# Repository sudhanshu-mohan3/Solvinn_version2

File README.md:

# VerveFlo

Pneumatic Compression Therapy Device firmware
ESP32-S3 · Arduino IDE

## Hardware
- ESP32-S3 Dev Module
- SH1106 OLED 128x64 (I2C)
- HX710B Pressure Sensor
- 5x Fill Solenoid Valves + 1x Release Valve (normally-open)
- 5V DC Pump Motor
- 2S 18650 Li-Ion Battery

## Pin Map
| Component       | GPIO |
|----------------|------|
| Fill Valve 1   | 26   |
| Fill Valve 2   | 47   |
| Fill Valve 3   | 39   |
| Fill Valve 4   | 40   |
| Fill Valve 5   | 41   |
| Release Valve  | 42   |
| Pump Motor     | 21   |
| HX710B Dout    | 34   |
| HX710B SCK     | 33   |
| LED            | 3    |
| Battery ADC    | 15   |
| BTN Start      | 35   |
| BTN Mode       | 36   |
| BTN Pressure   | 37   |
| BTN Time       | 48   |

## Libraries Required
- U8g2 by olikraus
- Q2HX711 by bogde (Queuetue_HX711_Library)
- WiFi / WebServer / DNSServer / Preferences — built into ESP32 core

## Board Settings
- Board: ESP32S3 Dev Module
- USB CDC On Boot: Enabled
- Partition: Default 4MB with spiffs

## Files
| File | Purpose |
|------|---------|
| verveflo.ino | Main firmware — flash this |
| verveflo_hwtest.ino | Hardware test — no libraries needed |
| verveflo_pressure_cal.ino | Pressure sensor calibration |
| verveflo_valve_test.ino | Valve test with OLED |

## First Time Setup
1. Flash verveflo.ino
2. Connect phone to WiFi hotspot: VerveFlo-Setup
3. Open 192.168.4.1 → enter your WiFi password
4. Open browser → http://[device IP]
5. Serial: type zero at atmosphere
6. Serial: type selftest to verify hardware

## Serial Monitor
115200 baud · Newline line ending
Type help for full command list

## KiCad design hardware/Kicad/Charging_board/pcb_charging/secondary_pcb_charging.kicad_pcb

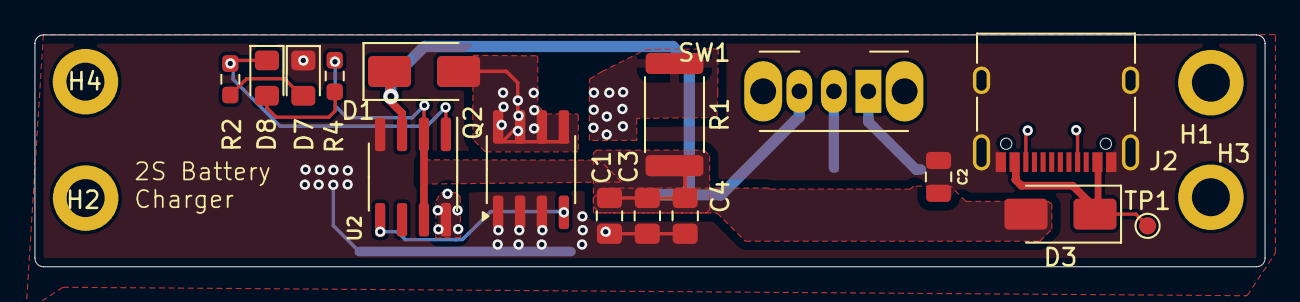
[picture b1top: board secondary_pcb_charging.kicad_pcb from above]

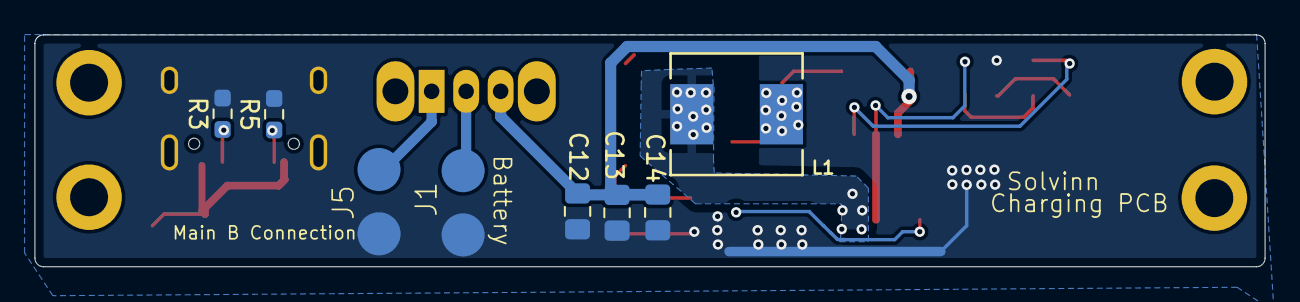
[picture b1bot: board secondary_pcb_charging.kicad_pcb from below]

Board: 2 copper layers, 71.3 x 13.4 mm, 28 parts (8 on the bottom side), 14 nets.

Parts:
C1, C3, C4, C12, C13, C14: 100nf; C_0805_2012Metric_Pad1.18x1.45mm_HandSolder
C2: 1uF_0805; C_0805_2012Metric
D1: SS34; D_SMA
D3: SS14; D_SMA
D7: RED LED; LED_0805_2012Metric_Pad1.15x1.40mm_HandSolder
D8: GREEN LED; LED_0805_2012Metric_Pad1.15x1.40mm_HandSolder
H1, H2, H3, H4: MountingHole; MountingHole_2.2mm_M2_DIN965_Pad
J1, J5: JST-S2B-XH_Sideentry; Solder_pad2
J2: USB_C_Receptacle_USB2.0_16P; USB_C_Receptacle_XKB_U262-16XN-4BVC11
L1: 10uh; LMLP07A7M1R0DTAS_AVX
Q2: IRF7832; SOIC-8_3.9x4.9mm_P1.27mm
R1: 50mohm_2512; R_2512
R2, R4: 2.2k; R_0603_1608Metric_Pad0.98x0.95mm_HandSolder
R3, R5: 5.1K; R_0603_1608Metric_Pad0.98x0.95mm_HandSolder
SW1: SW_Slide_SPDT_Straight_CK_OS102011MS2Q; SW_Slide_SPDT_Angled_CK_OS102011MA1Q
TP1: TestPoint; TestPoint_Pad_D1.0mm
U2: CN3302; SOIC-8_3.9x4.9mm_P1.27mm

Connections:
/8.4: J5.2, SW1.1 (C)
/ Battery_out: J1.2, SW1.2 (B)
/VBAT: C12.2, C13.2, C14.2, D1.1 (K), SW1.3 (A), U2.3 (BAT)
/cc1: J2.A5 (CC1), R3.1
/cc2: J2.B5 (CC2), R5.1
GND: C1.2, C2.1, C2.2, C3.2, C4.2, C12.1, C13.1, C14.1, D7.1 (K), J1.1, J2.A1 (GND), J2.A12 (GND), J2.B1 (GND), J2.B12 (GND), J2.S1 (SHIELD), J5.1, Q2.1 (S), Q2.2 (S), Q2.3 (S), R3.2, R5.2, U2.4 (GND)
unnamed: D1.2 (A), L1.2, Q2.5 (D), Q2.6 (D), Q2.7 (D), Q2.8 (D)
unnamed: D3.1 (K), J2.A4 (VBUS), J2.A9 (VBUS), J2.B4 (VBUS), J2.B9 (VBUS), TP1.1
unnamed: D7.2 (A), R2.1
unnamed: D8.2 (A), R4.1
unnamed: D8.1 (K), R2.2, U2.1 (STAT)
unnamed: Q2.4 (G), U2.5 (LDRV)
unnamed: L1.1, R1.1, U2.8 (CSN)
VBUS: C1.1, C3.1, C4.1, D3.2 (A), R1.2, R4.2, U2.2 (CE), U2.7 (VIN)

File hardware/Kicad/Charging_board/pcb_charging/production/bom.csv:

Designator,Footprint,Quantity,Value,LCSC Part #
"C1, C12, C13, C14, C3, C4",0805,6,100nf,
C2,0805,1,1uF_0805,
D1,D_SMA,1,SS34,
D3,D_SMA,1,SS14,
D7,0805,1,RED LED,
D8,0805,1,GREEN LED,
"J1, J5",Solder_pad2,2,JST-S2B-XH_Sideentry,
J2,USB_C_Receptacle_XKB_U262-16XN-4BVC11,1,USB_C_Receptacle_USB2.0_16P,
L1,LMLP07A7M1R0DTAS_AVX,1,10uh,
Q2,SOIC-8_3.9x4.9mm_P1.27mm,1,IRF7832,
R1,R_2512,1,50mohm_2512,
"R2, R4",0603,2,2.2k,
"R3, R5",0603,2,5.1K,
SW1,SW_Slide_SPDT_Angled_CK_OS102011MA1Q,1,SW_Slide_SPDT_Straight_CK_OS102011MS2Q,
TP1,TestPoint_Pad_D1.0mm,1,TestPoint,
U2,SOIC-8_3.9x4.9mm_P1.27mm,1,CN3302,

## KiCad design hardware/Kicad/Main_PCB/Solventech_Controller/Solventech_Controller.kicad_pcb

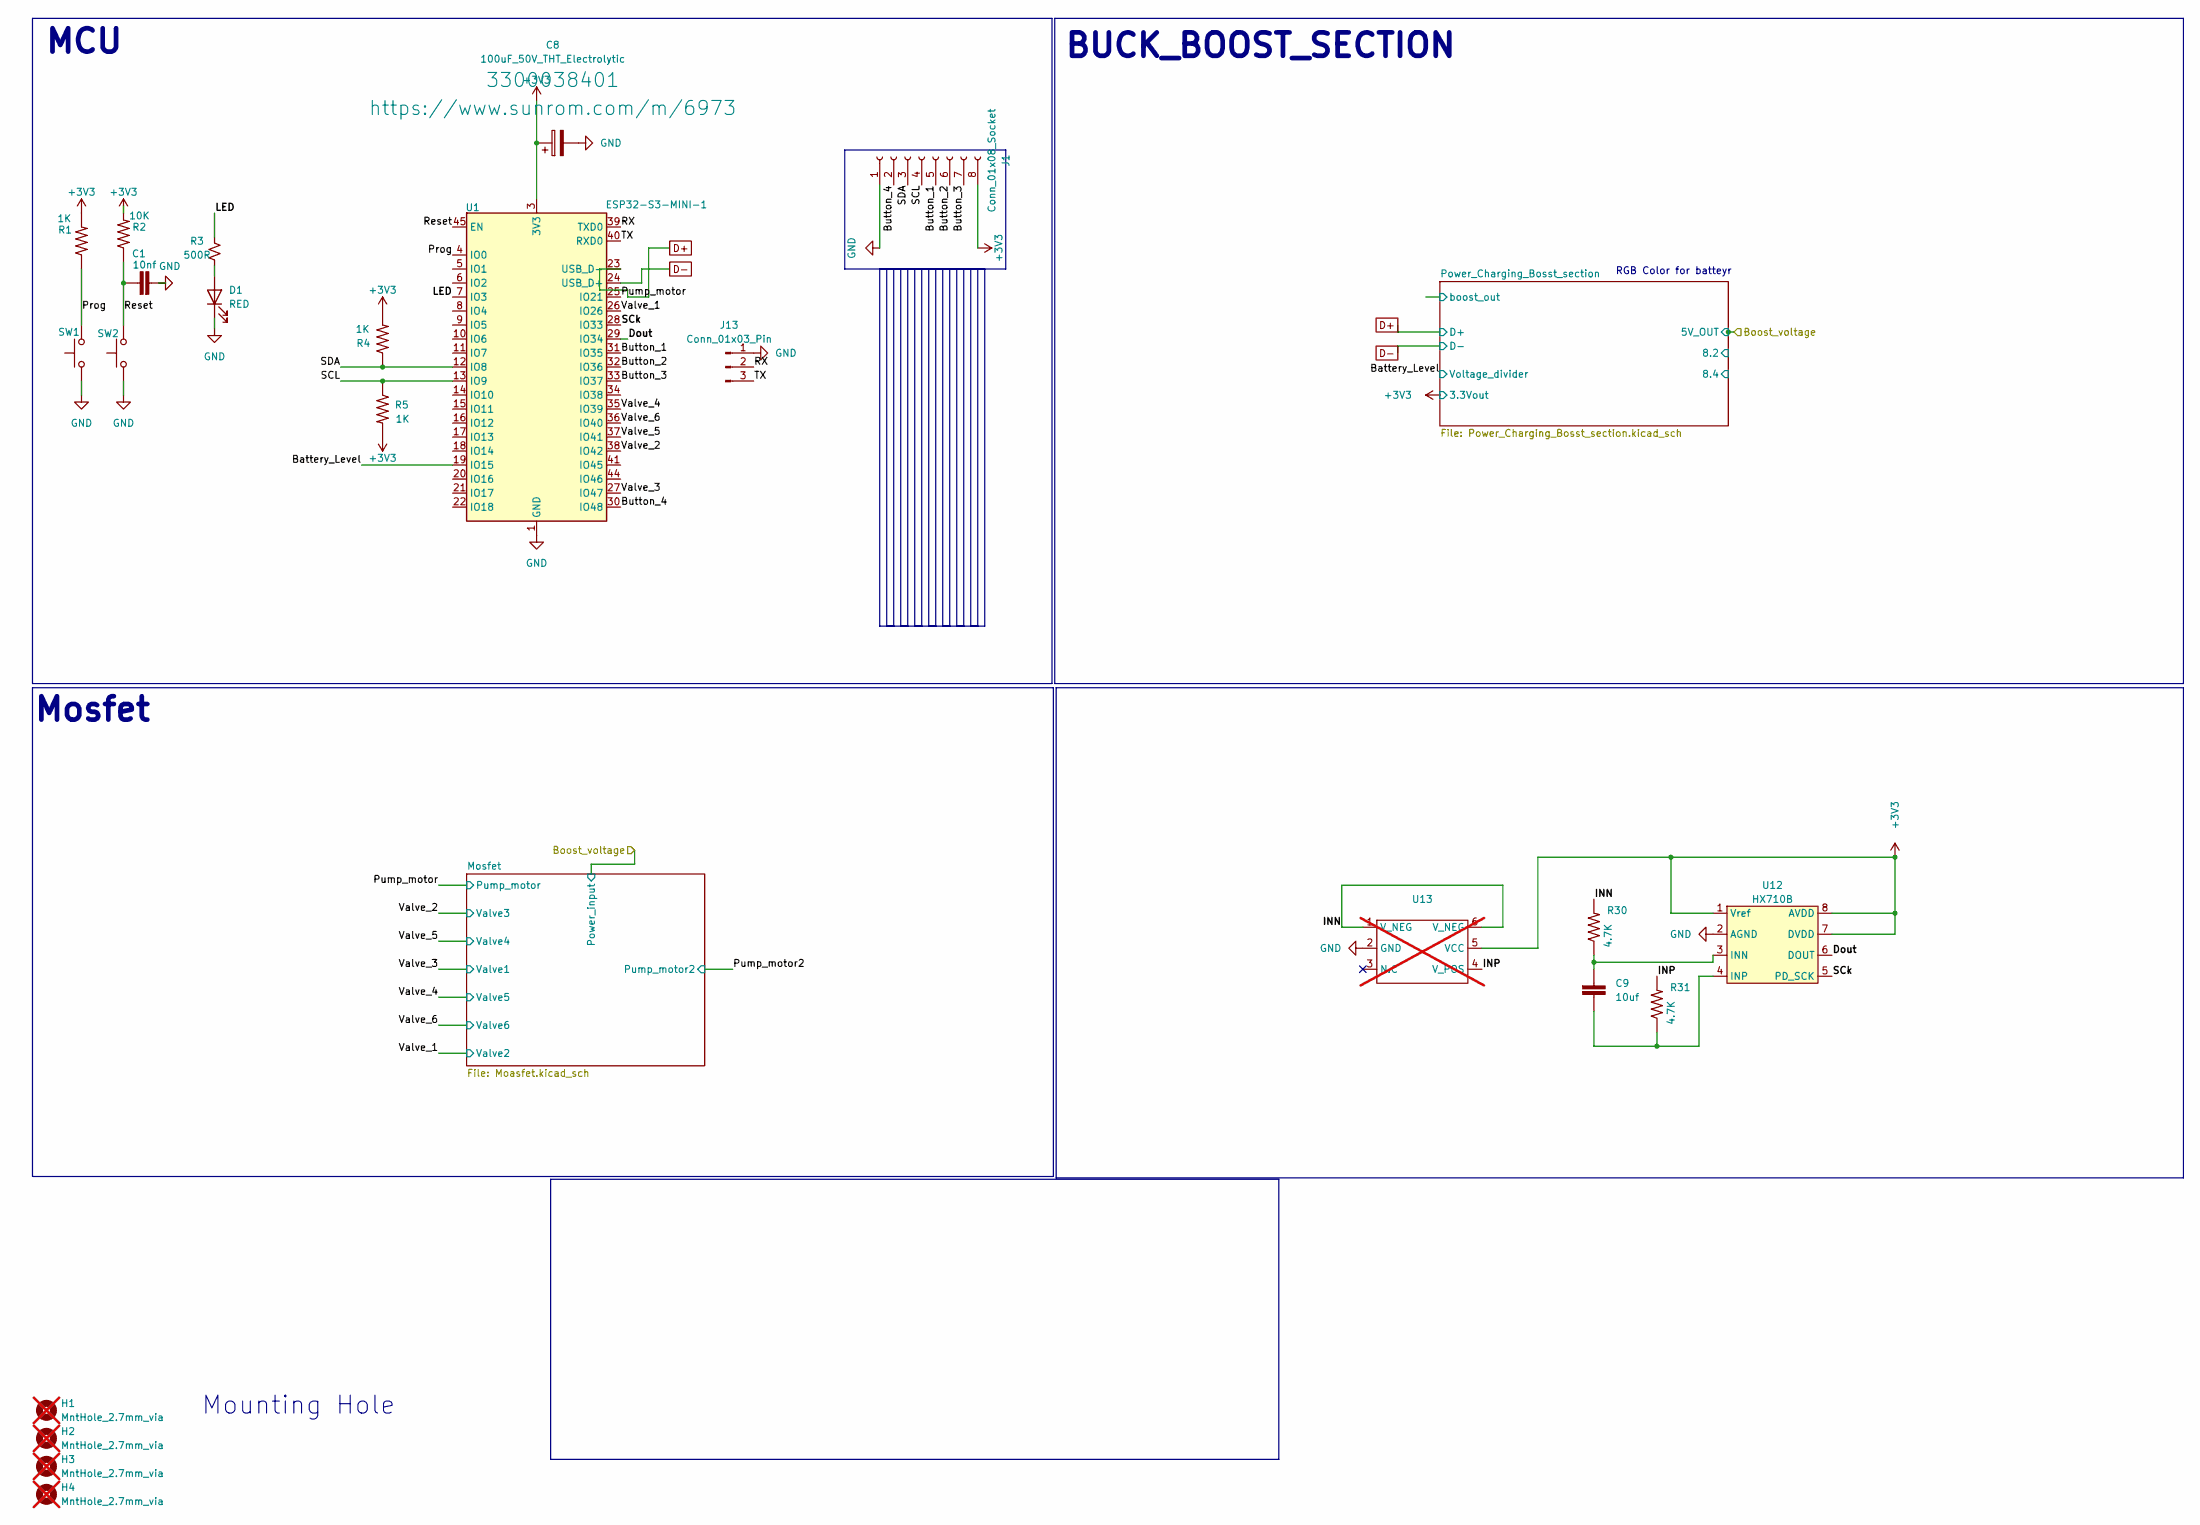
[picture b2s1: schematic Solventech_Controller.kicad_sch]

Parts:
C1: 10nf; Cap_0603_1608Metric
C8: 100uF_50V_THT_Electrolytic; CP_Elec_5x3; Morphle Part no. 3300038401
C9: 10uf; Cap_0603_1608Metric
D1: RED; LED_0603_1608Metric; LCSC C71911
H1, H2, H3, H4: MntHole_2.7mm_via; MountingHole_2.2mm_M2_DIN965; not fitted
J1: Conn_01x08_Socket; FFC_Connector_8pos
J13: Conn_01x03_Pin; JST_XH_B3B-XH-AM_1x03_P2.50mm_Vertical; MPN B3B-XH-AM_1x03
R1, R4, R5: 1K; R_0603_1608Metric
R2: 10K; R_0603_1608Metric
R3: 500R; R_0603_1608Metric; LCSC C25905
R30, R31: 4.7K; R_0603_1608Metric
SW1, SW2: SW_Push; SKRPABE010; MPN SKRPABE010; LCSC C720477
U1: ESP32-S3-MINI-1; ESP32-S2-MINI-1; MPN ESP32-S3-MINI-1
U12: HX710B; SOIC-8_3.9x4.9mm_P1.27mm; MPN HX710B
U13: Untitled; not fitted

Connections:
+3V3: C8.1, J1.8, R1.2, R2.2, R4.2, R5.2, U1.3 (3V3), U12.1 (Vref), U12.7 (DVDD), U12.8 (AVDD), U13.5 (VCC); also elsewhere on the board
/Battery_Level: U1.19 (IO15); also elsewhere on the board
/Button_1: J1.5, U1.31 (IO35)
/Button_2: J1.6, U1.32 (IO36)
/Button_3: J1.7, U1.33 (IO37)
/Button_4: J1.2, U1.30 (IO48)
/Dout: U1.29 (IO34), U12.6 (DOUT)
/INN: R30.2, U13.1 (V_NEG), U13.6 (V_NEG)
/INP: R31.2, U13.4 (V_POS)
/LED: R3.2, U1.7 (IO3)
/Prog: R1.1, SW1.2, U1.4 (IO0)
/Pump_motor: U1.25 (IO21); also elsewhere on the board
/RX: J13.2, U1.39 (TXD0)
/Reset: C1.1, R2.1, SW2.2, U1.45 (EN)
/SCL: J1.4, R5.1, U1.13 (IO9)
/SCk: U1.28 (IO33), U12.5 (PD_SCK)
/SDA: J1.3, R4.1, U1.12 (IO8)
/TX: J13.3, U1.40 (RXD0)
/Valve_1: U1.26 (IO26); also elsewhere on the board
/Valve_2: U1.38 (IO42); also elsewhere on the board
/Valve_3: U1.27 (IO47); also elsewhere on the board
/Valve_4: U1.35 (IO39); also elsewhere on the board
/Valve_5: U1.37 (IO41); also elsewhere on the board
/Valve_6: U1.36 (IO40); also elsewhere on the board
D+: U1.23 (USB_D-); also elsewhere on the board
D-: U1.24 (USB_D+); also elsewhere on the board
GND: C1.2, C8.2, D1.1 (K), J1.1, J13.1, SW1.1, SW2.1, U1.1 (GND), U1.2 (GND), U1.42 (GND), U1.43 (GND), U1.46 (GND), U1.47 (GND), U1.48 (GND), U1.49 (GND), U1.50 (GND), U1.51 (GND), U1.52 (GND), U1.53 (GND), U1.54 (GND), U1.55 (GND), U1.56 (GND), U1.57 (GND), U1.58 (GND), U1.59 (GND), U1.60 (GND), U1.61 (GND), U1.62 (GND), U1.63 (GND), U1.64 (GND), U1.65 (GND), U12.2 (AGND), U13.2 (GND); also elsewhere on the board
unnamed: D1.2 (A), R3.1
unnamed: C9.1, R30.1, U12.3 (INN)
unnamed: C9.2, R31.1, U12.4 (INP)

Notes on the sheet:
Mosfet
MCU
RGB Color for batteyr
BUCK_BOOST_SECTION
Mounting Hole

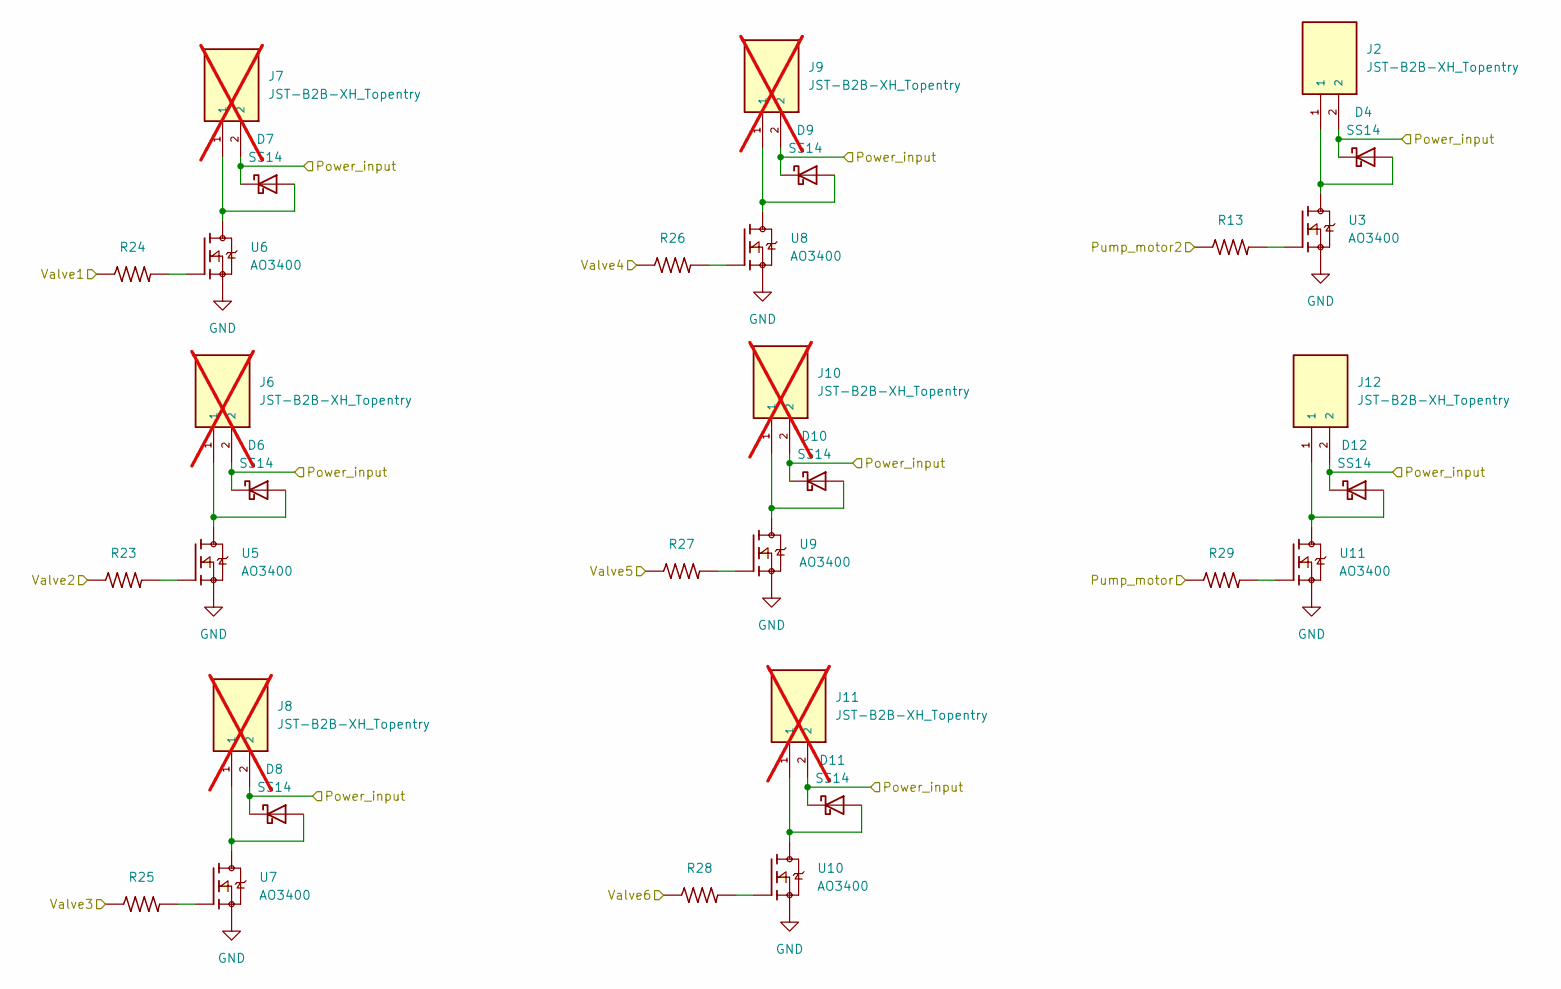
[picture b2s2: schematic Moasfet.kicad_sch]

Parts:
D4, D6, D7, D8, D9, D10, D11, D12: SS14; D_SMA; MPN SS14
J2, J12: JST-B2B-XH_Topentry; JST_PH_S2B-PH-SM4-TB_1x02-1MP_P2.00mm_Horizontal; Morphle Part no. 3300043701
J6, J7, J8, J9, J10, J11: JST-B2B-XH_Topentry; Solder_pad2; Morphle Part no. 3300043701; not fitted
R13, R23, R24, R25, R26, R27, R28, R29: 33R; R_0603_1608Metric
U3, U5, U6, U7, U8, U9, U10, U11: AO3400; SOT-23; MPN AO3400

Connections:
/Boost_voltage: D4.1 (K), D6.1 (K), D7.1 (K), D8.1 (K), D9.1 (K), D10.1 (K), D11.1 (K), D12.1 (K), J2.2, J6.2, J7.2, J8.2, J9.2, J10.2, J11.2, J12.2; also elsewhere on the board
/Pump_motor: R29.1; also elsewhere on the board
/Pump_motor2: R13.1
/Valve_1: R23.1; also elsewhere on the board
/Valve_2: R25.1; also elsewhere on the board
/Valve_3: R24.1; also elsewhere on the board
/Valve_4: R27.1; also elsewhere on the board
/Valve_5: R26.1; also elsewhere on the board
/Valve_6: R28.1; also elsewhere on the board
GND: U3.2, U5.2, U6.2, U7.2, U8.2, U9.2, U10.2, U11.2; also elsewhere on the board
unnamed: D4.2 (A), J2.1, U3.3
unnamed: D6.2 (A), J6.1, U5.3
unnamed: D7.2 (A), J7.1, U6.3
unnamed: D8.2 (A), J8.1, U7.3
unnamed: D9.2 (A), J9.1, U8.3
unnamed: D10.2 (A), J10.1, U9.3
unnamed: D11.2 (A), J11.1, U10.3
unnamed: D12.2 (A), J12.1, U11.3
unnamed: R13.2, U3.1
unnamed: R23.2, U5.1
unnamed: R24.2, U6.1
unnamed: R25.2, U7.1
unnamed: R26.2, U8.1
unnamed: R27.2, U9.1
unnamed: R28.2, U10.1
unnamed: R29.2, U11.1

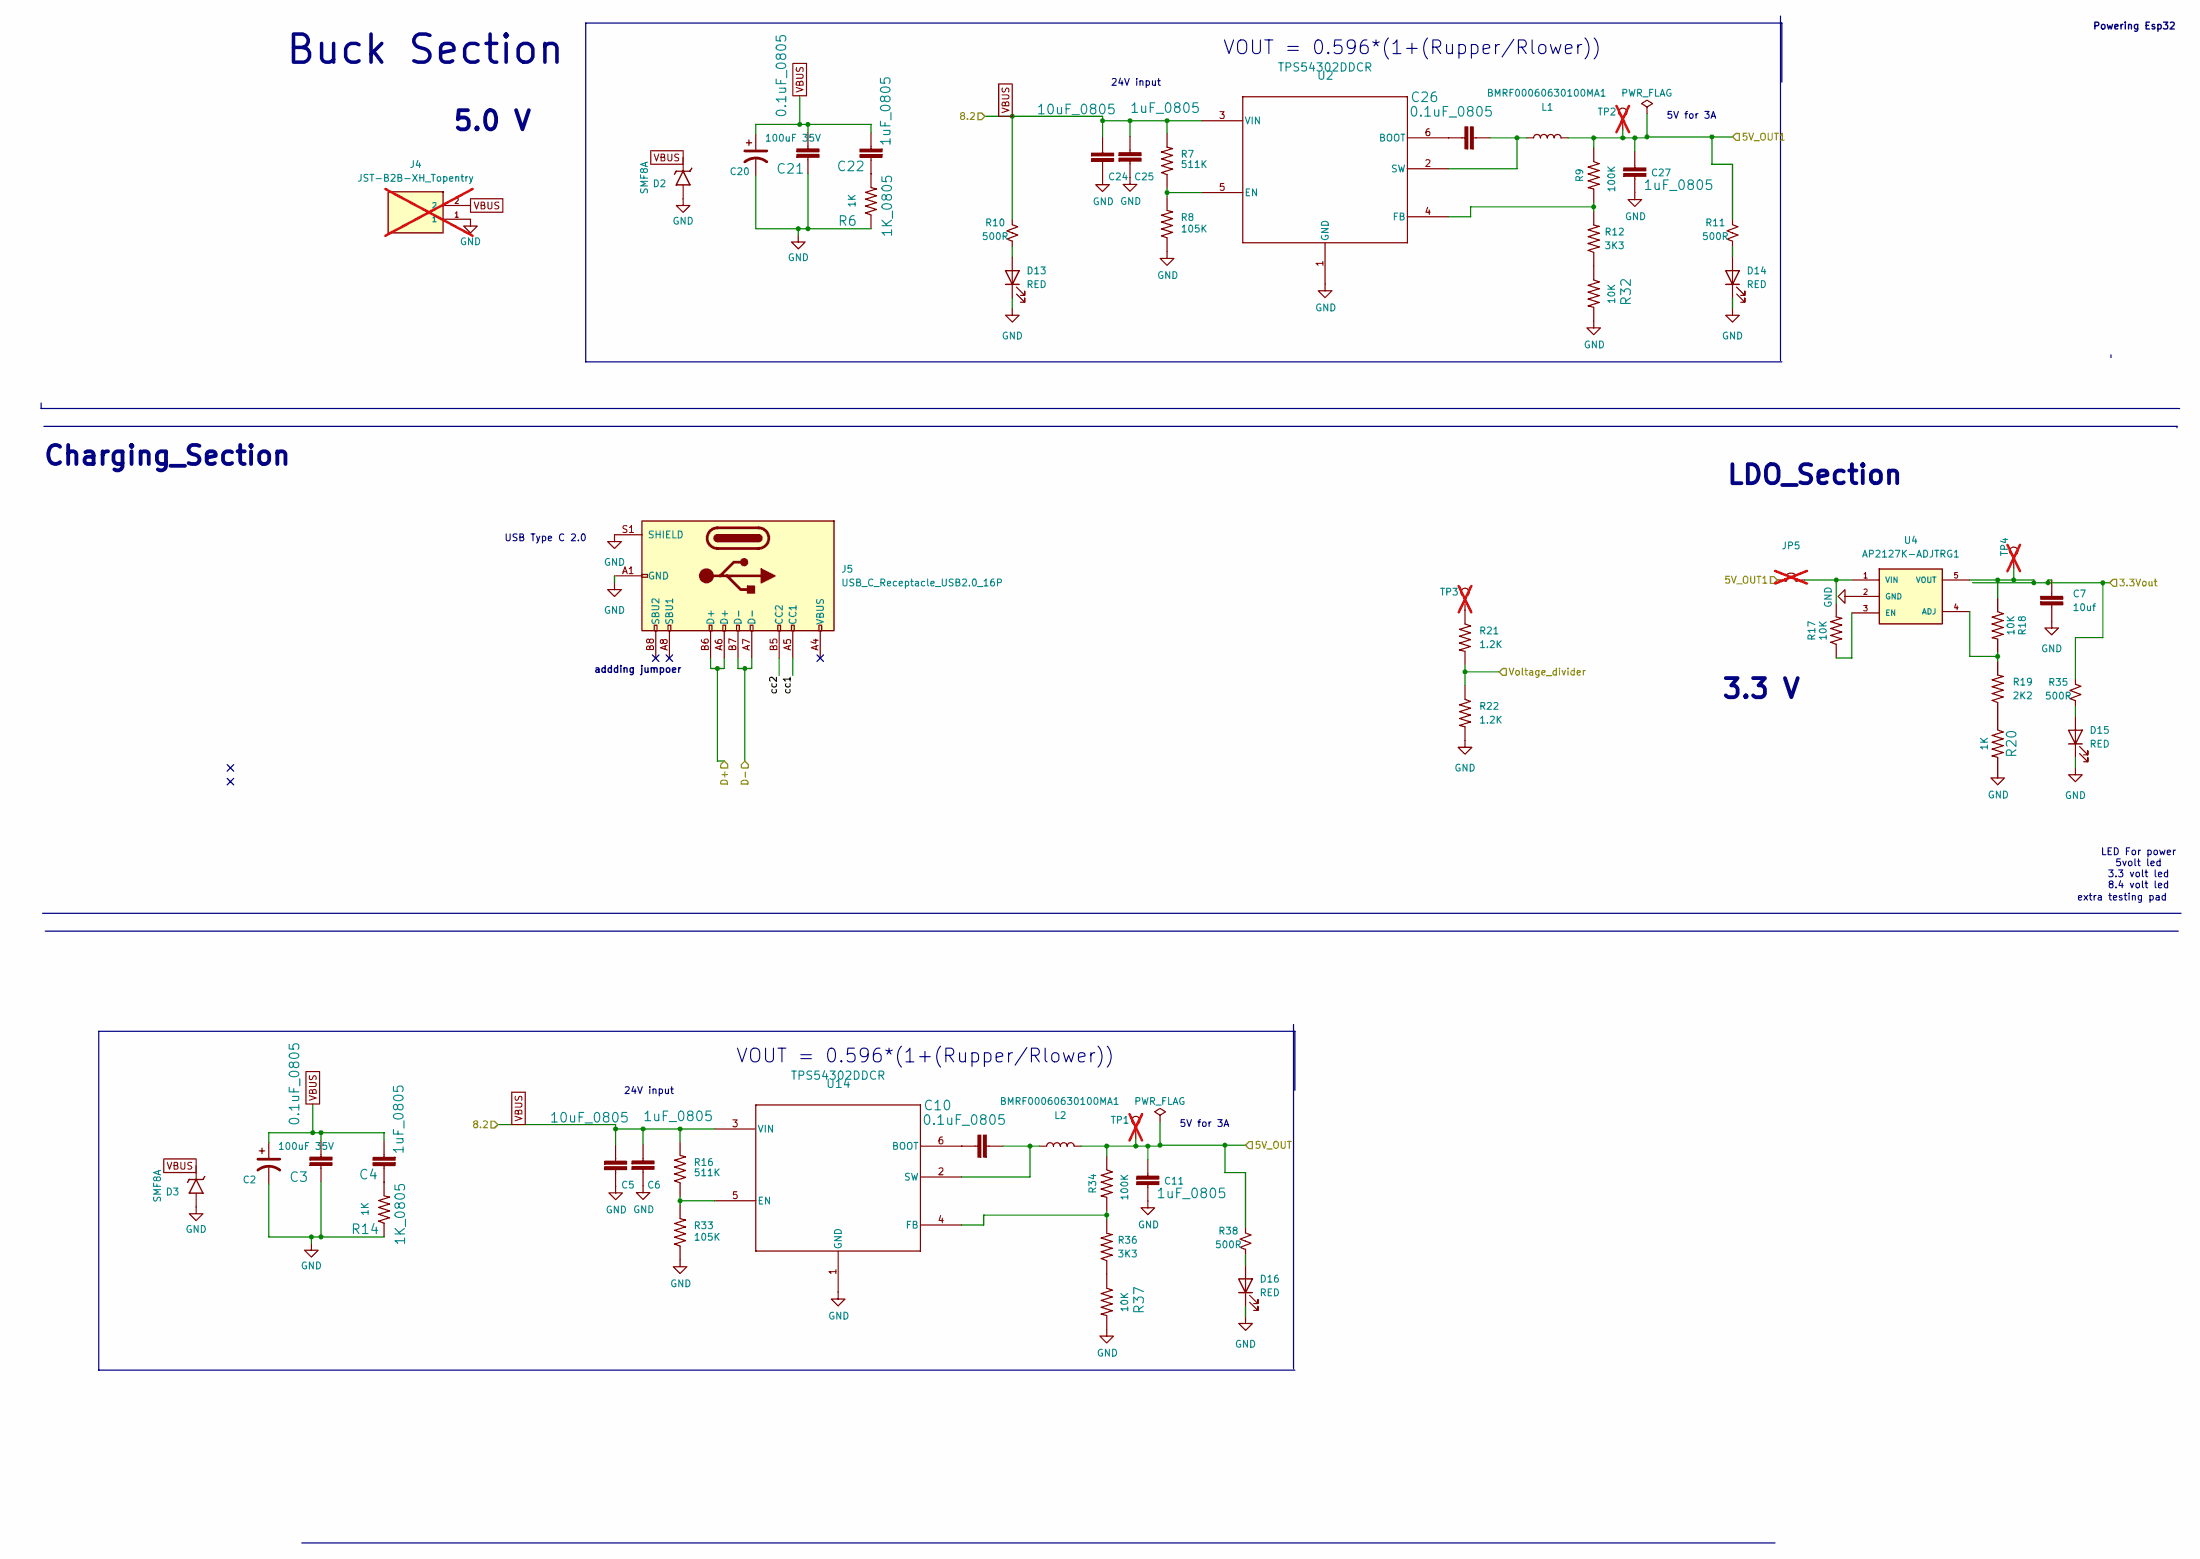
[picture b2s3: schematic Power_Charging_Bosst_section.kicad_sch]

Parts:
C2, C20: 100uF-35V; CP_EIA-2012-15_AVX-P; Morphle Part no. 3300036001
C3, C10, C21, C26: 0.1uF_0805; C_0805_2012Metric; Morphle Part no. 3300039201
C4, C6, C11, C22, C25, C27: 1uF_0805; C_0805_2012Metric; Morphle Part no. 3300039201
C5, C24: 10uF_0805; C_0805_2012Metric; Morphle Part no. 3300039201
C7: 10uf; Cap_0603_1608Metric
D2, D3: SMF8A; SOD123F; MPN SMF8A; Digi-Key Part Number F5824CT-ND
D13, D14, D15, D16: RED; LED_0603_1608Metric; LCSC C71911
J4: JST-B2B-XH_Topentry; Solder_pad2; Morphle Part no. 3300043701; not fitted
J5: USB_C_Receptacle_USB2.0_16P; USB_C_Receptacle_XKB_U262-16XN-4BVC11; MPN Receptacle_XKB_U262-16XN-4BVC11
JP5: Jumper_2_Small_Open; SolderJumper-2_P1.3mm_Open_RoundedPad1.0x1.5mm; not fitted
L1, L2: BMRF00060630100MA1; LMLP07A7M1R0DTAS_AVX; MPN BMRF00060630100MA1; Digi-Key Part Number 553-BMRF00060630100MA1CT-ND
R6, R14: 1K_0805; R_0805_2012Metric; Morphle Part no. 3300044701
R7, R16: 511K_0603; R_0603_1608Metric
R8, R33: 105K_0603; R_0603_1608Metric
R9, R34: 100K_0603; R_0603_1608Metric; Morphle Part no. 3300039401
R10, R11, R35, R38: 500R; R_0603_1608Metric; LCSC C25905
R12, R36: 3K3_0603; R_0603_1608Metric; Morphle Part no. 3300044501
R17, R18, R32, R37: 10K_0603; R_0603_1608Metric; Morphle Part no. 3300039401
R19: 2K2_0603; R_0603_1608Metric; Morphle Part no. 3300044501
R20: 1K_0603; R_0603_1608Metric; Morphle Part no. 3300039301
R21, R22: 1.2K; R_0603_1608Metric
TP1, TP2, TP3, TP4: TestPoint; TestPoint_Pad_D1.0mm; not fitted
U2, U14: TPS54302DDCR; SOT-23-6; MPN TPS54302DDCR; Digi-Key Part Number 296-46237-1-ND
U4: AP2127K-ADJTRG1; SOT-23-5; MPN AP2127K-ADJTRG1; Digi-Key Part Number AP2127K-ADJTRG1DICT-ND

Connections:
+3V3: C7.1, R18.1, R35.2, TP4.1, U4.5 (VOUT); also elsewhere on the board
/Battery_Level: R21.2, R22.1; also elsewhere on the board
/Boost_voltage: C11.1, L2.2, R34.1, R38.2, TP1.1; also elsewhere on the board
/Power_Charging_Bosst_section/5V_OUT1: C27.1, JP5.1 (A), L1.2, R9.1, R11.2, TP2.1
/Power_Charging_Bosst_section/cc1: J5.A5 (CC1)
/Power_Charging_Bosst_section/cc2: J5.B5 (CC2)
D+: J5.A6 (D+), J5.B6 (D+); also elsewhere on the board
D-: J5.A7 (D-), J5.B7 (D-); also elsewhere on the board
GND: C2.2, C3.2, C5.2, C6.2, C7.2, C11.2, C20.2, C21.2, C24.2, C25.2, C27.2, D2.2 (A), D3.2 (A), D13.1 (K), D14.1 (K), D15.1 (K), D16.1 (K), J4.1, J5.A1 (GND), J5.A12 (GND), J5.B1 (GND), J5.B12 (GND), J5.S1 (SHIELD), R6.1, R8.1, R14.1, R20.2, R22.2, R32.2, R33.1, R37.2, U2.1 (GND), U4.2 (GND), U14.1 (GND); also elsewhere on the board
unnamed: C4.1, R14.2
unnamed: C22.1, R6.2
unnamed: D13.2 (A), R10.1
unnamed: D14.2 (A), R11.1
unnamed: D15.2 (A), R35.1
unnamed: D16.2 (A), R38.1
unnamed: JP5.2 (B), R17.2, U4.1 (VIN)
unnamed: R12.1, R32.1
unnamed: R19.1, R20.1
unnamed: R21.1, TP3.1
unnamed: R36.1, R37.1
unnamed: C26.1, U2.6 (BOOT)
unnamed: R7.1, R8.2, U2.5 (EN)
unnamed: R9.2, R12.2, U2.4 (FB)
unnamed: C26.2, L1.1, U2.2 (SW)
unnamed: R18.2, R19.2, U4.4 (ADJ)
unnamed: R17.1, U4.3 (EN)
unnamed: C10.1, U14.6 (BOOT)
unnamed: R16.1, R33.2, U14.5 (EN)
unnamed: R34.2, R36.2, U14.4 (FB)
unnamed: C10.2, L2.1, U14.2 (SW)
VBUS: C2.1, C3.1, C4.2, C5.1, C6.1, C20.1, C21.1, C22.2, C24.1, C25.1, D2.1 (C), D3.1 (C), J4.2, R7.2, R10.2, R16.2, U2.3 (VIN), U14.3 (VIN)

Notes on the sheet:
24V input
5V for 3A
addding jumpoer
Powering Esp32
extra testing pad
LDO_Section
VOUT = 0.596*(1+(Rupper/Rlower))
5.0 V
Buck Section
USB Type C 2.0
LED For power 5volt led 3.3 volt led 8.4 volt led
Charging_Section
3.3 V

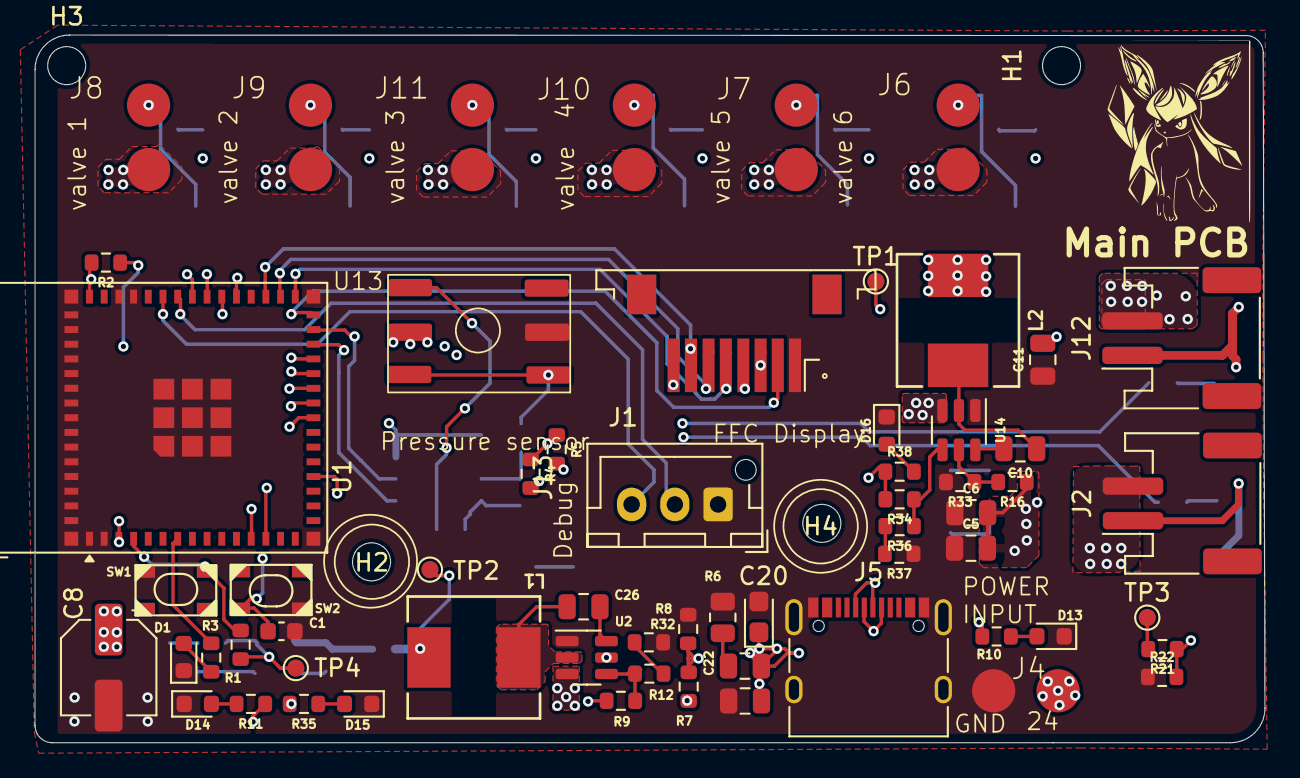
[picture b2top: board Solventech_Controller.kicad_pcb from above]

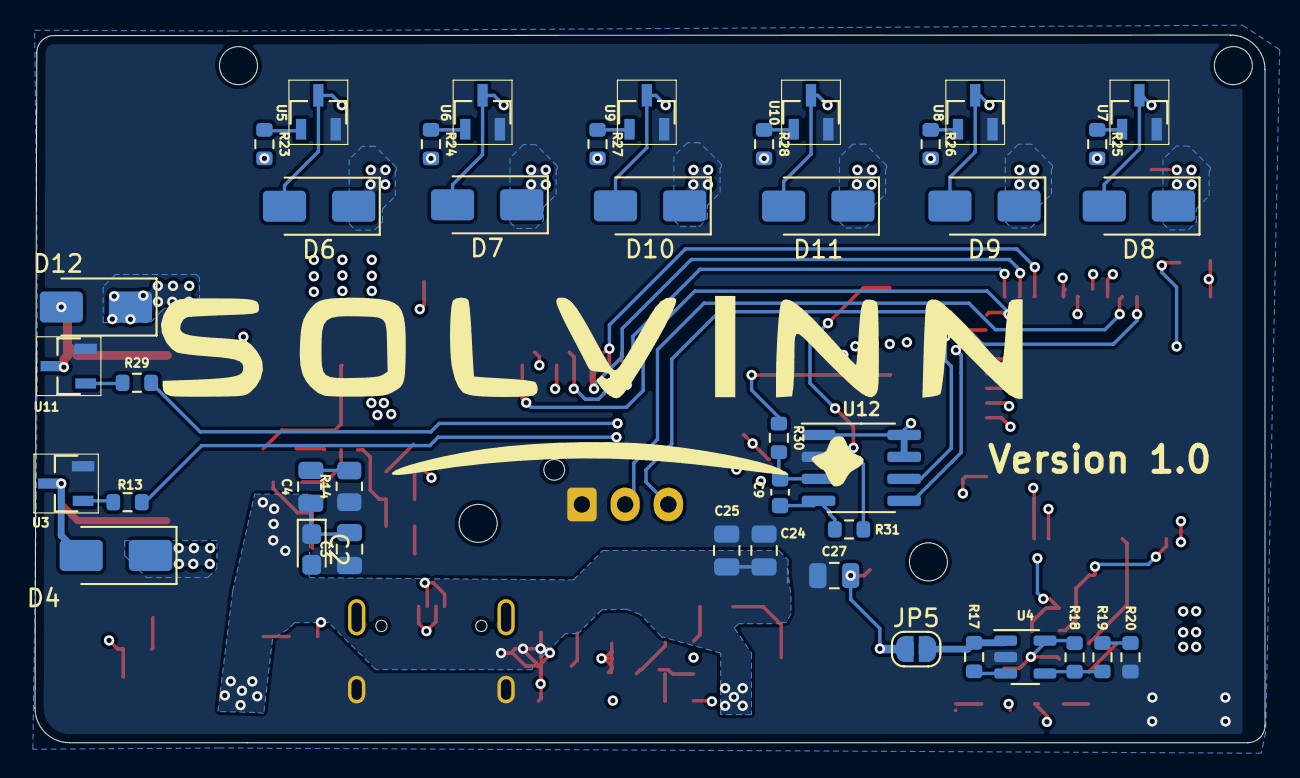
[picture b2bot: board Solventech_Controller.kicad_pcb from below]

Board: 4 copper layers, 71.1 x 40.9 mm, 106 parts (41 on the bottom side), 70 nets.

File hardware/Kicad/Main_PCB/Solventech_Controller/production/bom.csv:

Designator,Footprint,Quantity,Value,LCSC Part #
C1,0603,1,10nf,
"C10, C21, C26, C3",0805,4,0.1uF_0805,
"C11, C22, C25, C27, C4, C6",0805,6,1uF_0805,
"C2, C20",CP_EIA-2012-15_AVX-P,2,100uF-35V,CP_EIA-2012-15_AVX-P
"C24, C5",0805,2,10uF_0805,
C8,CP_Elec_5x3,1,100uF_50V_THT_Electrolytic,
C9,0603,1,10uf,
"D1, D13, D14, D15, D16",0603,5,RED,C71911
"D10, D11, D12, D4, D6, D7, D8, D9",D_SMA,8,SS14,SS14
J1,FFC_Connector_8pos,1,Conn_01x08_Socket,
J12,JST_PH_S2B-PH-SM4-TB_1x02-1MP_P2.00mm_Horizontal,1,JST-B2B-XH_Topentry,B3B-XH_Topentry
J13,JST_XH_B3B-XH-AM_1x03_P2.50mm_Vertical,1,Conn_01x03_Pin,B3B-XH-AM_1x03
J2,JST_PH_S2B-PH-SM4-TB_1x02-1MP_P2.00mm_Horizontal,1,JST-B2B-XH_Topentry,
J5,USB_C_Receptacle_XKB_U262-16XN-4BVC11,1,USB_C_Receptacle_USB2.0_16P,Receptacle_XKB_U262-16XN-4BVC11
"L1, L2",LMLP07A7M1R0DTAS_AVX,2,BMRF00060630100MA1,BMRF00060630100MA1
"R1, R4, R5",0603,3,1K,
"R10, R11, R3, R35, R38",0603,5,500R,C25905
"R12, R36",0603,2,3K3_0603,
"R13, R23, R24, R25, R26, R27, R28, R29",0603,8,33R,
"R14, R6",0805,2,1K_0805,
"R16, R7",0603,2,511K_0603,
"R17, R18, R32, R37",0603,4,10K_0603,
R19,0603,1,2K2_0603,
R2,0603,1,10K,
R20,0603,1,1K_0603,
"R21, R22",0603,2,1.2K,
"R30, R31",0603,2,4.7K,
"R33, R8",0603,2,105K_0603,
"R34, R9",0603,2,100K_0603,
"SW1, SW2",SKRPABE010,2,SW_Push,C720477
U1,ESP32-S2-MINI-1,1,ESP32-S3-MINI-1,ESP32-S3-MINI-1
"U10, U11, U3, U5, U6, U7, U8, U9",SOT-23,8,AO3400,AO3400
U12,SOIC-8_3.9x4.9mm_P1.27mm,1,HX710B,HX710B
"U14, U2",SOT-23-6,2,TPS54302DDCR,TPS54302DDCR
U4,SOT-23-5,1,AP2127K-ADJTRG1,AP2127K-ADJTRG1

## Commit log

2026-06-02 ssudhansu
2026-06-02 add kicad and ino codes
